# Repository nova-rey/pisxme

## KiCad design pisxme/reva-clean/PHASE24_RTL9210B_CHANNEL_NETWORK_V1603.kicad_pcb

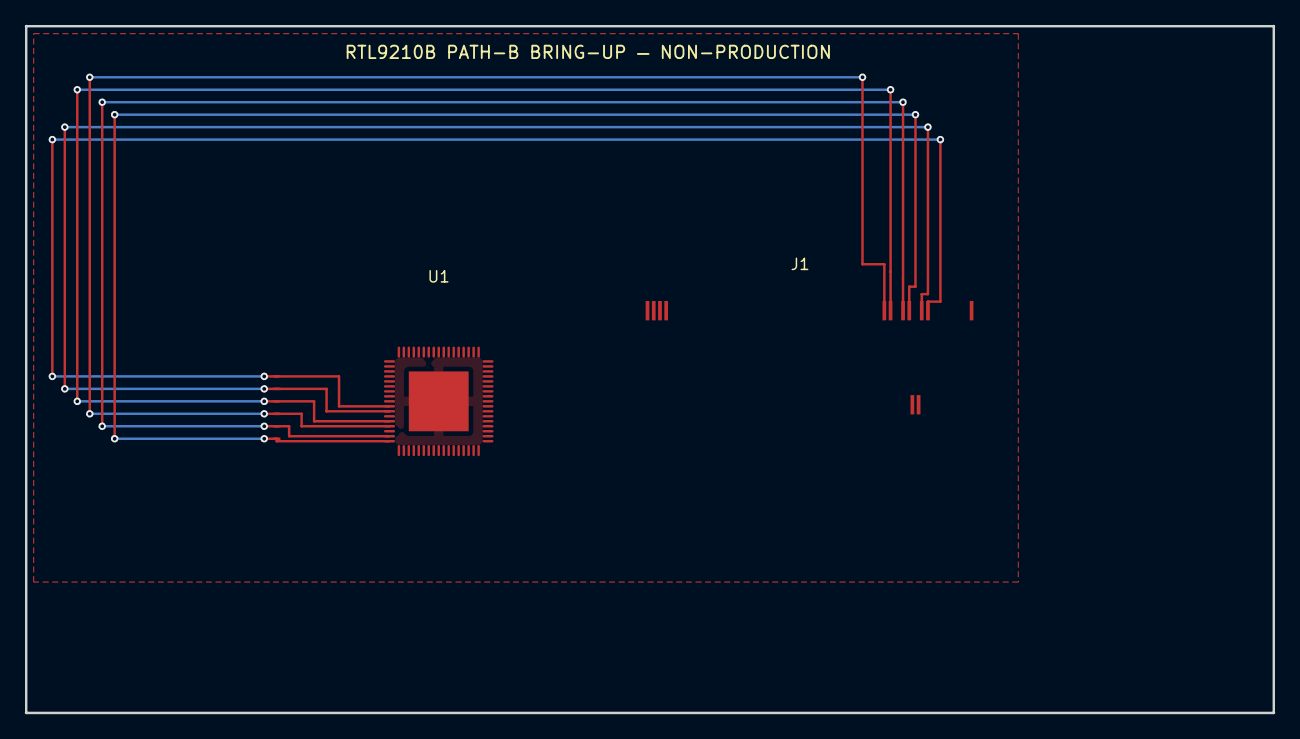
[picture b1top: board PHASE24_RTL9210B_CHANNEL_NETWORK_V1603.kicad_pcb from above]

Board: 6 copper layers, 100.1 x 55.1 mm, 3 parts (0 on the bottom side), 14 nets.

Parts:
J1: M.2 Socket 3 M-key 2280; BRINGUP_M2_MKEY
JH1: QFN_ESCAPE_HANDOFF
U1: RTL9210B-CG; RTL9210B-CG_QUALIFICATION

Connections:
CLKREQ_N: J1.52, U1.13
GND: U1.45, U1.66, U1.69
LANE0_RXN: J1.41, JH1.65, U1.65
LANE0_RXP: J1.43, JH1.64, U1.64
LANE0_TXN: J1.47, JH1.67, U1.67
LANE0_TXP: J1.49, JH1.68, U1.68
PEDET: J1.69, U1.8
PERST_N: J1.50, U1.14
REFCLK_N: J1.53, JH1.62, U1.62
REFCLK_P: J1.55, JH1.61, U1.61
RTL_1V1: U1.16, U1.25, U1.36, U1.40, U1.50, U1.55, U1.60, U1.63
RTL_3V3: U1.20, U1.34, U1.39, U1.52
RTL_5V: U1.17, U1.33
SSD_3V3: J1.2, J1.4, J1.6, J1.8

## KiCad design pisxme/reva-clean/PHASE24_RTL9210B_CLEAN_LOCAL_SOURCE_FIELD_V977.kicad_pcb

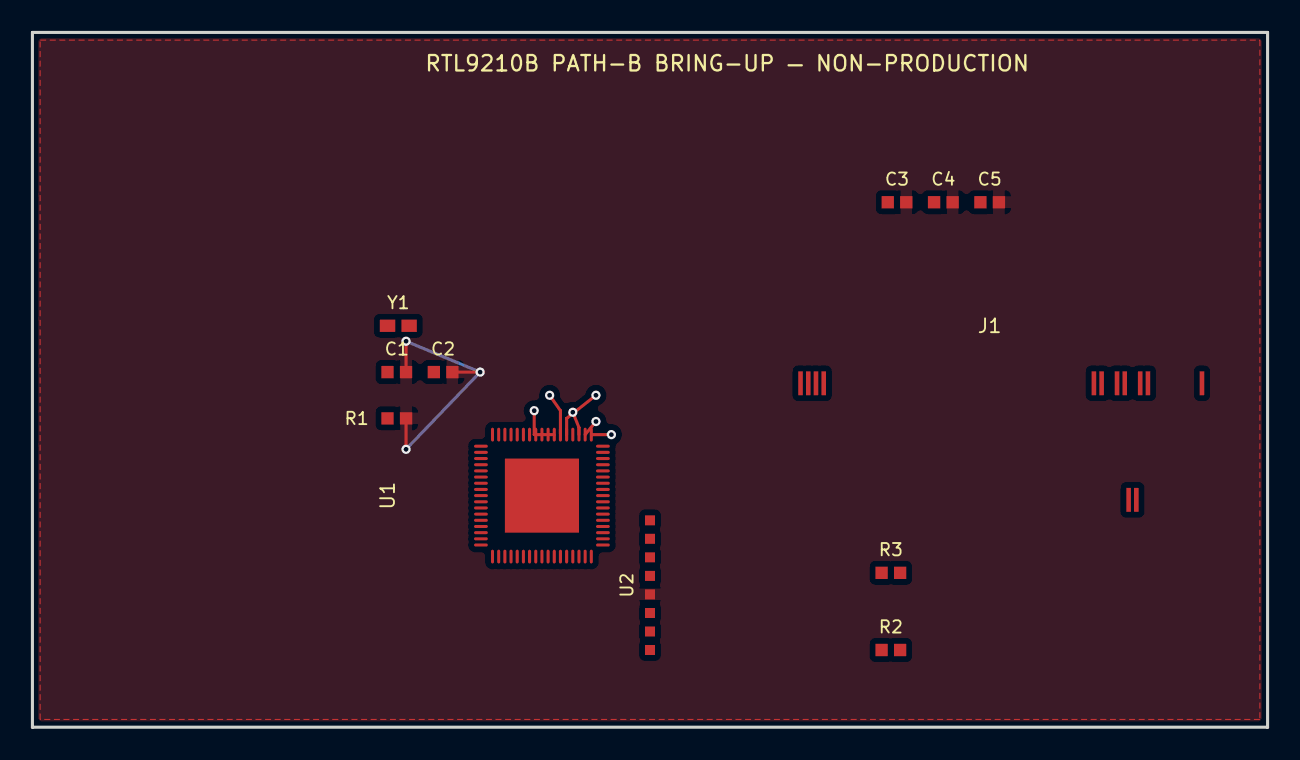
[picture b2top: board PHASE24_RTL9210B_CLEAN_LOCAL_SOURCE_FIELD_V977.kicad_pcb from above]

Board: 6 copper layers, 80.0 x 45.0 mm, 12 parts (0 on the bottom side), 22 nets.

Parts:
C1: 16pF_XTAL_IN; BRINGUP_16pF_XTAL_IN
C2: 16pF_XTAL_OUT; BRINGUP_16pF_XTAL_OUT
C3: RTL_3V3_DEC; BRINGUP_RTL_3V3_DEC
C4: RTL_1V1_DEC; BRINGUP_RTL_1V1_DEC
C5: RTL_5V_DEC; BRINGUP_RTL_5V_DEC
J1: M.2 Socket 3 M-key 2280; BRINGUP_M2_MKEY
R1: 12k_RSET; BRINGUP_12k_RSET
R2: PEDET_PULLUP; BRINGUP_PEDET_PULLUP
R3: CLKREQ_PULLUP; BRINGUP_CLKREQ_PULLUP
U1: RTL9210B-CG; RTL9210B-CG_QUALIFICATION
U2: W25Q128_SPI_FLASH; BRINGUP_W25Q128_SPI_FLASH
Y1: XTAL_25MHz; BRINGUP_XTAL_25MHz

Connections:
CLKREQ_N: J1.52, R3.1, U1.13
GND: C1.2, C2.2, C3.2, C4.2, C5.2, R1.2, U1.45, U1.66, U1.69, U2.4
LANE0_RXN: J1.41, U1.65
LANE0_RXP: J1.43, U1.64
LANE0_TXN: J1.47, U1.67
LANE0_TXP: J1.49, U1.68
PEDET: J1.69, R2.1, U1.8
PERST_N: J1.50, U1.14
REFCLK_N: J1.53, U1.62
REFCLK_P: J1.55, U1.61
RSET: R1.1, U1.51
RTL_1V1: C4.1, U1.16, U1.25, U1.36, U1.40, U1.50, U1.55, U1.60, U1.63
RTL_3V3: C3.1, R2.2, R3.2, U1.20, U1.34, U1.39, U1.52, U2.3, U2.8
RTL_5V: C5.1, U1.17, U1.33
SPICLK: U1.19, U2.6
SPICS: U1.24, U2.1
SPISI: U1.18, U2.5
SPISO: U1.23, U2.2
SPISO3: U1.22, U2.7
SSD_3V3: J1.2, J1.4, J1.6, J1.8
XTAL_IN: C1.1, U1.53, Y1.1
XTAL_OUT: C2.1, U1.54, Y1.2
